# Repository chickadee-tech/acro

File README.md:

# Chickadee Tech Acro Polystack Mod #
This mod connects an MPU-6500 to the base control board. It is not in active production.

## Documentation ##
See the [wiki](https://github.com/chickadee-tech/acro/wiki) for documentation.

## Polystack ##
This **mod** board is part of the Polystack platform for modular microcontrol systems. More information on the platform can be found at [polystack.org](http://polystack.org).

## Support ##
If you need support with a board you own or have development questions please email support@chickadee.tech or check [chickadee.tech/support](https://chickadee.tech/support) for other ways to get support.

## Contributing ##
Please note that this project is released with a [Contributor Code of Conduct](CODE_OF_CONDUCT.md). By participating in this project you agree to abide by its terms.

### Setup ###
Components and footprints for PCB parts are not included in this repository. Instead, checkout the [chickadee-tech/kicad-libs](https://github.com/chickadee-tech/kicad-libs) repository in the same directory that this repository is checked out in. All part definitions should be relative so that they will load correctly.

### Pull requests ###
For fixes please submit a pull request to the original repository. After the pull request is merged, check the [Chickadee Tech Active Contributor Discount (ACD)](https://chickadee.tech/active-contributor) to see if you are eligible for a discount code to use on your next purchase.

### Derivatives ###
If developing your own version of the Acro board please remove all Chickadee Tech trademarks and follow the [CC-BY license](LICENSE). While not required, please consider open sourcing your modifications so others can learn from your improvements. If you do email support@chickadee.tech and we may choose to add your project to the ACD.

You may also license the Polystack logo for free by emailing support@chickadee.tech. We'll ask for your gerbers to ensure the design complies with specifications laid out [here](https://github.com/chickadee-tech/polystack/wiki) and provide written permission to use the trademark after compliance has been demonstrated.

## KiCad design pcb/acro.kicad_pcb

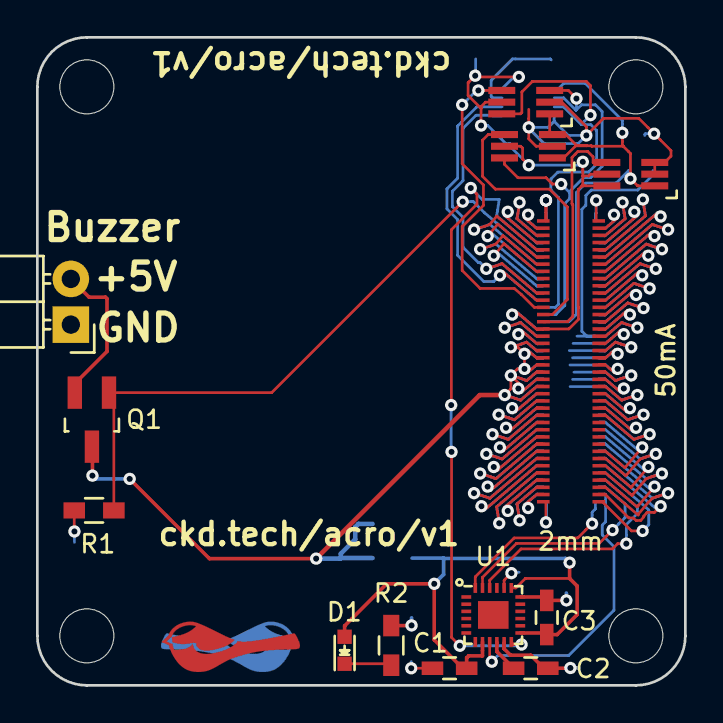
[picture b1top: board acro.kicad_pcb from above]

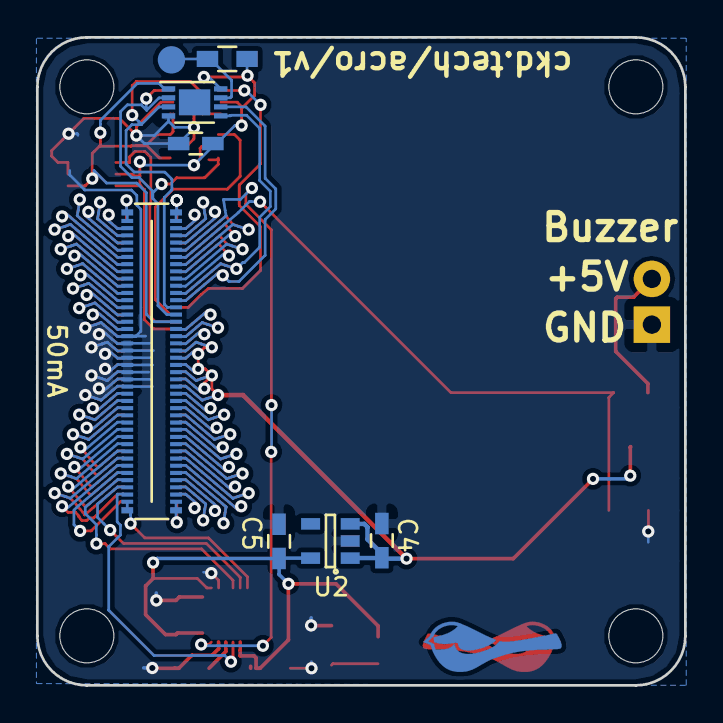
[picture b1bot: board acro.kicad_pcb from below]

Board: 2 copper layers, 36.0 x 36.0 mm, 21 parts (8 on the bottom side), 76 nets.

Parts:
C1: 10nF; C_0603_HandSoldering
C2, C3: 0.1uF; C_0603_HandSoldering
C4, C5: 1uF; C_0603_HandSoldering
D1: LED; LED-0603
P1: CONN_01X02; Pin_Header_Angled_1x02
PORT_ANDOR1: SN74LVC1G0832; SC-70-6_Handsoldering
PORT_C1: 0.1uF; C_0603_HandSoldering
PORT_IC1: AT24CS02-MAHM; DFN-8-1EP_3x2mm_Pitch0.5mm
PORT_IN1: CKD_SANDWICH; DF40-80pin-Header
PORT_INV1: SN74LVC1G58; SC-70-6_Handsoldering
PORT_OUT1: CKD_SANDWICH; DF40-3-4mm-80pin-Receptacle
PORT_P1: CONN_01X01; Measurement_Point_Round-SMD-Pad_Small
PORT_R1: 10k; R_0603_HandSoldering
PORT_XOR1: SN74LVC1G58; SC-70-6_Handsoldering
Q1: Q_NMOS_GSD; SOT-23_Handsoldering
R1: 100k; R_0603_HandSoldering
R2: 1k; R_0603_HandSoldering
U1: MPU-6500; QFN-24-1EP_3x3mm_Pitch0.4mm
U2: TLV70233DBV; SOT-23-5

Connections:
+3V3: C1.1, C3.1, C5.1, D1.2, U1.8, U1.13, U1.19, U2.5
+5V: C4.1, PORT_IN1.19, PORT_IN1.20, PORT_IN1.21, PORT_IN1.22, PORT_IN1.23, PORT_IN1.24, PORT_OUT1.19, PORT_OUT1.20, PORT_OUT1.21, PORT_OUT1.22, PORT_OUT1.23, PORT_OUT1.24, Q1.3, U2.1, U2.3
/ExpansionPort/3V3_0.3A_E: PORT_IN1.17, PORT_OUT1.17
/ExpansionPort/3V3_0.3A_LL: PORT_ANDOR1.5, PORT_C1.1, PORT_IC1.8, PORT_IN1.16, PORT_INV1.5, PORT_INV1.6, PORT_OUT1.16, PORT_R1.2, PORT_XOR1.5
/ExpansionPort/+BATT: PORT_IN1.18, PORT_OUT1.18
/ExpansionPort/ADC1: PORT_IN1.49, PORT_OUT1.49
/ExpansionPort/ADC2: PORT_IN1.50, PORT_OUT1.50
/ExpansionPort/BOOT: PORT_IN1.65, PORT_OUT1.65
/ExpansionPort/CAN_HI: PORT_IN1.67, PORT_OUT1.67
/ExpansionPort/CAN_LO: PORT_IN1.68, PORT_OUT1.68
/ExpansionPort/GPIO1: PORT_IN1.5, U1.12
/ExpansionPort/GPIO2: PORT_IN1.6, Q1.1, R1.1
/ExpansionPort/GPIO3: PORT_IN1.7, PORT_OUT1.5
/ExpansionPort/GPIO4: PORT_IN1.8, PORT_OUT1.6
/ExpansionPort/GPIO5: PORT_IN1.9, PORT_OUT1.7
/ExpansionPort/GPIO6: PORT_IN1.10, PORT_OUT1.8
/ExpansionPort/HEIGHT_1: PORT_ANDOR1.1, PORT_IC1.1, PORT_IN1.15, PORT_INV1.1, PORT_XOR1.1, PORT_XOR1.3
/ExpansionPort/HEIGHT_2: PORT_ANDOR1.3, PORT_IC1.2, PORT_IN1.14, PORT_XOR1.6
/ExpansionPort/HEIGHT_4: PORT_ANDOR1.6, PORT_IC1.3, PORT_IN1.13
/ExpansionPort/NEW_HEIGHT_1: PORT_INV1.4, PORT_OUT1.15
/ExpansionPort/NEW_HEIGHT_2: PORT_OUT1.14, PORT_XOR1.4
/ExpansionPort/NEW_HEIGHT_4: PORT_ANDOR1.4, PORT_OUT1.13
/ExpansionPort/RESET: PORT_IN1.66, PORT_OUT1.66
/ExpansionPort/SDMMC1_CK: PORT_IN1.55, PORT_OUT1.55
/ExpansionPort/SDMMC1_CMD: PORT_IN1.56, PORT_OUT1.56
/ExpansionPort/SDMMC1_D0: PORT_IN1.51, PORT_OUT1.51
/ExpansionPort/SDMMC1_D1: PORT_IN1.52, PORT_OUT1.52
/ExpansionPort/SDMMC1_D2: PORT_IN1.53, PORT_OUT1.53
/ExpansionPort/SDMMC1_D3: PORT_IN1.54, PORT_OUT1.54
/ExpansionPort/SPI1_MISO: PORT_IN1.79, U1.9
/ExpansionPort/SPI1_MOSI: PORT_IN1.80, U1.24
/ExpansionPort/SPI1_NSS: PORT_IN1.77, U1.22
/ExpansionPort/SPI1_SCK: PORT_IN1.78, U1.23
/ExpansionPort/SPI2_MISO: PORT_IN1.75, PORT_OUT1.79
/ExpansionPort/SPI2_MOSI: PORT_IN1.76, PORT_OUT1.80
/ExpansionPort/SPI2_NSS: PORT_IN1.73, PORT_OUT1.77
/ExpansionPort/SPI2_SCK: PORT_IN1.74, PORT_OUT1.78
/ExpansionPort/SPI3_MISO: PORT_IN1.71, PORT_OUT1.75
/ExpansionPort/SPI3_MOSI: PORT_IN1.72, PORT_OUT1.76
/ExpansionPort/SPI3_NSS: PORT_IN1.69, PORT_OUT1.73
/ExpansionPort/SPI3_SCK: PORT_IN1.70, PORT_OUT1.74
/ExpansionPort/TIM1: PORT_IN1.1, PORT_OUT1.1
/ExpansionPort/TIM2: PORT_IN1.2, PORT_OUT1.2
/ExpansionPort/TIM3: PORT_IN1.3, PORT_OUT1.3
/ExpansionPort/TIM4: PORT_IN1.4, PORT_OUT1.4
/ExpansionPort/TIMG1_CH1: PORT_IN1.41, PORT_OUT1.41
/ExpansionPort/TIMG1_CH2: PORT_IN1.42, PORT_OUT1.42
/ExpansionPort/TIMG1_CH3: PORT_IN1.43, PORT_OUT1.43
/ExpansionPort/TIMG1_CH4: PORT_IN1.44, PORT_OUT1.44
/ExpansionPort/TIMG2_CH1: PORT_IN1.45, PORT_OUT1.45
/ExpansionPort/TIMG2_CH2: PORT_IN1.46, PORT_OUT1.46
/ExpansionPort/TIMG2_CH3: PORT_IN1.47, PORT_OUT1.47
/ExpansionPort/TIMG2_CH4: PORT_IN1.48, PORT_OUT1.48
/ExpansionPort/UART1_RX: PORT_IN1.40, PORT_OUT1.40
/ExpansionPort/UART1_TX: PORT_IN1.39, PORT_OUT1.39
/ExpansionPort/UART2_RX: PORT_IN1.38, PORT_OUT1.38
/ExpansionPort/UART2_TX: PORT_IN1.37, PORT_OUT1.37
/ExpansionPort/UART3_RX: PORT_IN1.36, PORT_OUT1.36
/ExpansionPort/UART3_TX: PORT_IN1.35, PORT_OUT1.35
/ExpansionPort/UART4_RX: PORT_IN1.34, PORT_OUT1.34
/ExpansionPort/UART4_TX: PORT_IN1.33, PORT_OUT1.33
/ExpansionPort/UART5_RX: PORT_IN1.32, PORT_OUT1.32
/ExpansionPort/UART5_TX: PORT_IN1.31, PORT_OUT1.31
/ExpansionPort/UART6_RX: PORT_IN1.30, PORT_OUT1.30
/ExpansionPort/UART6_TX: PORT_IN1.29, PORT_OUT1.29
/ExpansionPort/UART7_RX: PORT_IN1.28, PORT_OUT1.28
/ExpansionPort/UART7_TX: PORT_IN1.27, PORT_OUT1.27
/ExpansionPort/UART8_RX: PORT_IN1.26, PORT_OUT1.26
/ExpansionPort/UART8_TX: PORT_IN1.25, PORT_OUT1.25
/ExpansionPort/i2c_SCL: PORT_IC1.6, PORT_IN1.12, PORT_OUT1.12
/ExpansionPort/i2c_SDA: PORT_IC1.5, PORT_IN1.11, PORT_OUT1.11
GNDPWR: C1.2, C2.2, C3.2, C4.2, C5.2, P1.1, PORT_ANDOR1.2, PORT_C1.2, PORT_IC1.4, PORT_IN1.57, PORT_IN1.58, PORT_IN1.59, PORT_IN1.60, PORT_IN1.61, PORT_IN1.62, PORT_IN1.63, PORT_IN1.64, PORT_INV1.2, PORT_INV1.3, PORT_OUT1.57, PORT_OUT1.58, PORT_OUT1.59, PORT_OUT1.60, PORT_OUT1.61, PORT_OUT1.62, PORT_OUT1.63, PORT_OUT1.64, PORT_XOR1.2, R1.2, R2.2, U1.11, U1.18, U1.20, U2.2
unnamed: C2.1, U1.10
unnamed: D1.1, R2.1
unnamed: P1.2, Q1.2
unnamed: PORT_IC1.7, PORT_P1.1, PORT_R1.1

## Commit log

2015-12-21 v1 of the acro module
2016-01-07 change pull up resistor value
2016-07-07 Add license information to many files. PCB design files are CC-BY and code is MIT license.
2016-07-07 Add back .gitignore after repo split.
2016-07-07 Convert to relative component and footprint paths.
2016-07-08 Add README, LICENSE and code of conduct.
2016-07-08 Correct README links
2016-07-08 Don't use https for polystack.org
2016-07-08 Add BOM
2016-07-08 Change column header in BOM

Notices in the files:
pcb/acro.kicad_pcb:
Copyright 2016 Chickadee Tech LLC,
This work is licensed under the Creative Commons Attribution 4.0 International License.
To view a copy of this license, visit http://creativecommons.org/licenses/by/4.0
or send a letter to Creative Commons, PO Box 1866, Mountain View, CA 94042, USA.
